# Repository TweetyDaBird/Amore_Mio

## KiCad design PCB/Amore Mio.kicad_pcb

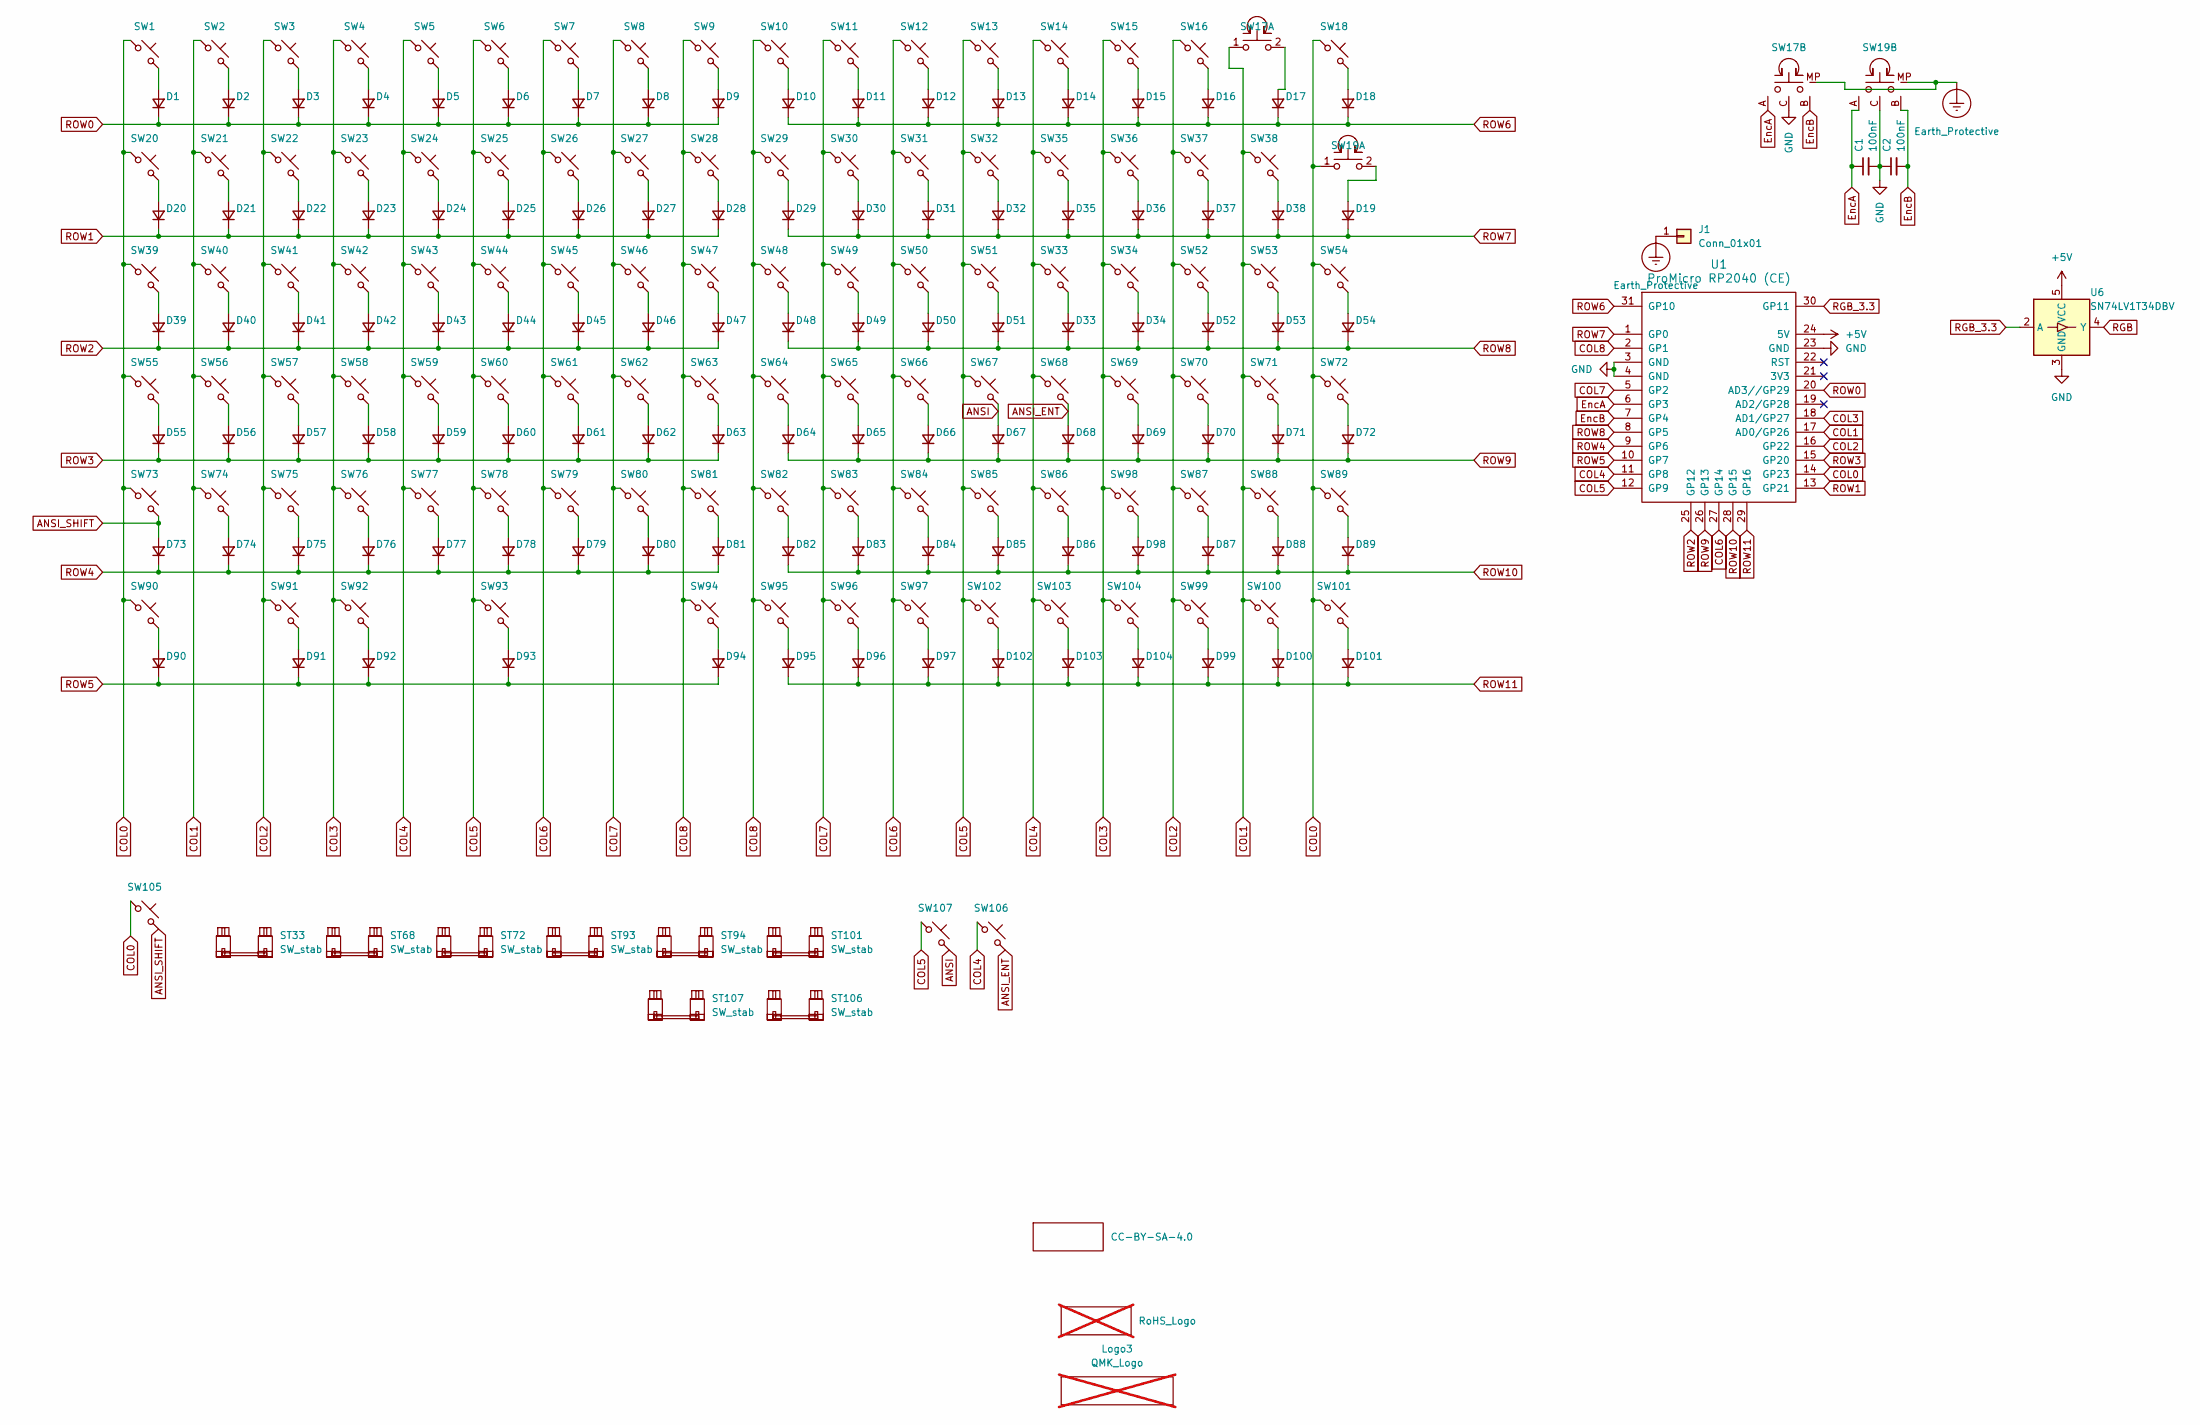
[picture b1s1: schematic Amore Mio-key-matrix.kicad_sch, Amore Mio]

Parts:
C1, C2: 100nF; C_Axial_L5.1mm_D3.1mm_P7.50mm_Horizontal; LCSC C513772
D1, D2, D3, D4, D5, D6, D7, D8, D9, D10, D11, D12, D13, D14, D15, D16, D17, D18, D19, D20, D21, D22, D23, D24, D25, D26, D27, D28, D29, D30, D31, D32, D33, D34, D35, D36, D37, D38, D39, D40, D41, D42, D43, D44, D45, D46, D47, D48, D49, D50, D51, D52, D53, D54, D55, D56, D57, D58, D59, D60, D61, D62, D63, D64, D65, D66, D67, D68, D69, D70, D71, D72, D73, D74, D75, D76, D77, D78, D79, D80, D81, D82, D83, D84, D85, D86, D87, D88, D89, D90, D91, D92, D93, D94, D95, D96, D97, D98, D99, D100, D101, D102, D103, D104: D; D_SOD-123
J1: Conn_01x01; PinHeader_1x01_P2.54mm_Vertical
Logo1: CC-BY-SA-4.0; CC_BY_SA_40_line
Logo2: RoHS_Logo; RoHs; not fitted
Logo3: QMK_Logo; Powered_by_QMK; not fitted
ST33, ST68, ST72, ST93, ST94, ST101, ST106, ST107: SW_stab; Stabilizer_Cherry_MX_2.00u
SW1, SW2, SW3, SW4, SW5, SW6, SW7, SW8, SW9, SW10, SW11, SW12, SW13, SW14, SW15, SW16, SW18, SW20, SW21, SW22, SW23, SW24, SW25, SW26, SW27, SW28, SW29, SW30, SW31, SW32, SW34, SW35, SW36, SW37, SW38, SW40, SW41, SW42, SW43, SW44, SW45, SW46, SW47, SW48, SW49, SW50, SW51, SW52, SW53, SW54, SW56, SW57, SW58, SW59, SW60, SW61, SW62, SW63, SW64, SW65, SW66, SW67, SW69, SW70, SW71, SW74, SW75, SW76, SW77, SW78, SW79, SW80, SW81, SW82, SW83, SW84, SW85, SW87, SW88, SW89, SW96, SW98, SW99, SW100, SW102, SW103, SW104: SW_Push; SW_MX_HotSwap
SW17, SW19: SW_Push; SW_MX_HotSwap_Encoder
SW33: SW_Push; SW_MX_HotSwap_2.00u
SW39, SW90, SW107: SW_Push; SW_MX_HotSwap_1.50u
SW55, SW86: SW_Push; SW_MX_HotSwap_1.75u
SW68: SW_Push; SW_MX_HotSwap_ISO_Enter_flipped
SW72, SW101: SW_Push; SW_MX_HotSwap_Vertical_2.00u
SW73, SW91, SW92, SW95, SW97: SW_Push; SW_MX_HotSwap_1.25u
SW93, SW105, SW106: SW_Push; SW_MX_HotSwap_2.25u
SW94: SW_Push; SW_MX_HotSwap_2.75u
U1: ProMicro RP2040 (CE); ProMicro RP2040CE
U6: SN74LV1T34DBV; SOT-23-5; LCSC C100024

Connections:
+5V: U1.24 (5V), U6.5 (VCC); also elsewhere on the board
ANSI: D67.2 (A), SW67.2, SW107.2
ANSI_ENT: D68.2 (A), SW68.2, SW106.2
ANSI_SHIFT: D73.2 (A), SW73.2, SW105.2
COL0: SW1.1, SW18.1, SW19.1, SW19.S1, SW20.1, SW39.1, SW54.1, SW55.1, SW72.1, SW73.1, SW89.1, SW90.1, SW101.1, SW105.1, U1.14 (GP23)
COL1: SW2.1, SW17.1, SW17.S1, SW21.1, SW38.1, SW40.1, SW53.1, SW56.1, SW71.1, SW74.1, SW88.1, SW100.1, U1.17 (AD0/GP26)
COL2: SW3.1, SW16.1, SW22.1, SW37.1, SW41.1, SW52.1, SW57.1, SW70.1, SW75.1, SW87.1, SW91.1, SW99.1, U1.16 (GP22)
COL3: SW4.1, SW15.1, SW23.1, SW34.1, SW36.1, SW42.1, SW58.1, SW69.1, SW76.1, SW92.1, SW98.1, SW104.1, U1.18 (AD1/GP27)
COL4: SW5.1, SW14.1, SW24.1, SW33.1, SW35.1, SW43.1, SW59.1, SW68.1, SW77.1, SW86.1, SW103.1, SW106.1, U1.11 (GP8)
COL5: SW6.1, SW13.1, SW25.1, SW32.1, SW44.1, SW51.1, SW60.1, SW67.1, SW78.1, SW85.1, SW93.1, SW102.1, SW107.1, U1.12 (GP9)
COL6: SW7.1, SW12.1, SW26.1, SW31.1, SW45.1, SW50.1, SW61.1, SW66.1, SW79.1, SW84.1, SW97.1, U1.27 (GP14)
COL7: SW8.1, SW11.1, SW27.1, SW30.1, SW46.1, SW49.1, SW62.1, SW65.1, SW80.1, SW83.1, SW96.1, U1.5 (GP2)
COL8: SW9.1, SW10.1, SW28.1, SW29.1, SW47.1, SW48.1, SW63.1, SW64.1, SW81.1, SW82.1, SW94.1, SW95.1, U1.2 (GP1)
EncA: C1.1, SW17.A, SW19.A, U1.6 (GP3)
EncB: C2.2, SW17.B, SW19.B, U1.7 (GP4)
unnamed: D1.2 (A), SW1.2
unnamed: D2.2 (A), SW2.2
unnamed: D3.2 (A), SW3.2
unnamed: D4.2 (A), SW4.2
unnamed: D5.2 (A), SW5.2
unnamed: D6.2 (A), SW6.2
unnamed: D7.2 (A), SW7.2
unnamed: D8.2 (A), SW8.2
unnamed: D9.2 (A), SW9.2
unnamed: D10.2 (A), SW10.2
unnamed: D11.2 (A), SW11.2
unnamed: D12.2 (A), SW12.2
unnamed: D13.2 (A), SW13.2
unnamed: D14.2 (A), SW14.2
unnamed: D15.2 (A), SW15.2
unnamed: D16.2 (A), SW16.2
unnamed: D17.2 (A), SW17.2, SW17.S2
unnamed: D18.2 (A), SW18.2
unnamed: D19.2 (A), SW19.2, SW19.S2
unnamed: D20.2 (A), SW20.2
unnamed: D21.2 (A), SW21.2
unnamed: D22.2 (A), SW22.2
unnamed: D23.2 (A), SW23.2
unnamed: D24.2 (A), SW24.2
unnamed: D25.2 (A), SW25.2
unnamed: D26.2 (A), SW26.2
unnamed: D27.2 (A), SW27.2
unnamed: D28.2 (A), SW28.2
unnamed: D29.2 (A), SW29.2
unnamed: D30.2 (A), SW30.2
unnamed: D31.2 (A), SW31.2
unnamed: D32.2 (A), SW32.2
unnamed: D33.2 (A), SW33.2
unnamed: D34.2 (A), SW34.2
unnamed: D35.2 (A), SW35.2
unnamed: D36.2 (A), SW36.2
unnamed: D37.2 (A), SW37.2
unnamed: D38.2 (A), SW38.2
unnamed: D39.2 (A), SW39.2
unnamed: D40.2 (A), SW40.2
unnamed: D41.2 (A), SW41.2
unnamed: D42.2 (A), SW42.2
unnamed: D43.2 (A), SW43.2
unnamed: D44.2 (A), SW44.2
unnamed: D45.2 (A), SW45.2
unnamed: D46.2 (A), SW46.2
unnamed: D47.2 (A), SW47.2
unnamed: D48.2 (A), SW48.2
unnamed: D49.2 (A), SW49.2
unnamed: D50.2 (A), SW50.2
unnamed: D51.2 (A), SW51.2
unnamed: D52.2 (A), SW52.2
unnamed: D53.2 (A), SW53.2
unnamed: D54.2 (A), SW54.2
unnamed: D55.2 (A), SW55.2
unnamed: D56.2 (A), SW56.2
unnamed: D57.2 (A), SW57.2
unnamed: D58.2 (A), SW58.2
unnamed: D59.2 (A), SW59.2
unnamed: D60.2 (A), SW60.2
unnamed: D61.2 (A), SW61.2
unnamed: D62.2 (A), SW62.2
unnamed: D63.2 (A), SW63.2
unnamed: D64.2 (A), SW64.2
unnamed: D65.2 (A), SW65.2
unnamed: D66.2 (A), SW66.2
unnamed: D69.2 (A), SW69.2
unnamed: D70.2 (A), SW70.2
unnamed: D71.2 (A), SW71.2
unnamed: D72.2 (A), SW72.2
unnamed: D74.2 (A), SW74.2
unnamed: D75.2 (A), SW75.2
unnamed: D76.2 (A), SW76.2
unnamed: D77.2 (A), SW77.2
unnamed: D78.2 (A), SW78.2
unnamed: D79.2 (A), SW79.2
unnamed: D80.2 (A), SW80.2
unnamed: D81.2 (A), SW81.2
unnamed: D82.2 (A), SW82.2
unnamed: D83.2 (A), SW83.2
unnamed: D84.2 (A), SW84.2
unnamed: D85.2 (A), SW85.2
unnamed: D86.2 (A), SW86.2
unnamed: D87.2 (A), SW87.2
unnamed: D88.2 (A), SW88.2
unnamed: D89.2 (A), SW89.2
unnamed: D90.2 (A), SW90.2
unnamed: D91.2 (A), SW91.2
unnamed: D92.2 (A), SW92.2
unnamed: D93.2 (A), SW93.2
unnamed: D94.2 (A), SW94.2
unnamed: D95.2 (A), SW95.2
unnamed: D96.2 (A), SW96.2
unnamed: D97.2 (A), SW97.2
unnamed: D98.2 (A), SW98.2
unnamed: D99.2 (A), SW99.2
unnamed: D100.2 (A), SW100.2
unnamed: D101.2 (A), SW101.2
unnamed: D102.2 (A), SW102.2
unnamed: D103.2 (A), SW103.2
unnamed: D104.2 (A), SW104.2
RGB: U6.4 (Y); also elsewhere on the board
RGB_3.3: U1.30 (GP11), U6.2 (A)
ROW0: D1.1 (K), D2.1 (K), D3.1 (K), D4.1 (K), D5.1 (K), D6.1 (K), D7.1 (K), D8.1 (K), D9.1 (K), U1.20 (AD3//GP29)
ROW1: D20.1 (K), D21.1 (K), D22.1 (K), D23.1 (K), D24.1 (K), D25.1 (K), D26.1 (K), D27.1 (K), D28.1 (K), U1.13 (GP21)
ROW2: D39.1 (K), D40.1 (K), D41.1 (K), D42.1 (K), D43.1 (K), D44.1 (K), D45.1 (K), D46.1 (K), D47.1 (K), U1.25 (GP12)
ROW3: D55.1 (K), D56.1 (K), D57.1 (K), D58.1 (K), D59.1 (K), D60.1 (K), D61.1 (K), D62.1 (K), D63.1 (K), U1.15 (GP20)
ROW4: D73.1 (K), D74.1 (K), D75.1 (K), D76.1 (K), D77.1 (K), D78.1 (K), D79.1 (K), D80.1 (K), D81.1 (K), U1.9 (GP6)
ROW5: D90.1 (K), D91.1 (K), D92.1 (K), D93.1 (K), D94.1 (K), U1.10 (GP7)
ROW6: D10.1 (K), D11.1 (K), D12.1 (K), D13.1 (K), D14.1 (K), D15.1 (K), D16.1 (K), D17.1 (K), D18.1 (K), U1.31 (GP10)
ROW7: D19.1 (K), D29.1 (K), D30.1 (K), D31.1 (K), D32.1 (K), D35.1 (K), D36.1 (K), D37.1 (K), D38.1 (K), U1.1 (GP0)
ROW8: D33.1 (K), D34.1 (K), D48.1 (K), D49.1 (K), D50.1 (K), D51.1 (K), D52.1 (K), D53.1 (K), D54.1 (K), U1.8 (GP5)
ROW9: D64.1 (K), D65.1 (K), D66.1 (K), D67.1 (K), D68.1 (K), D69.1 (K), D70.1 (K), D71.1 (K), D72.1 (K), U1.26 (GP13)
ROW10: D82.1 (K), D83.1 (K), D84.1 (K), D85.1 (K), D86.1 (K), D87.1 (K), D88.1 (K), D89.1 (K), D98.1 (K), U1.28 (GP15)
ROW11: D95.1 (K), D96.1 (K), D97.1 (K), D99.1 (K), D100.1 (K), D101.1 (K), D102.1 (K), D103.1 (K), D104.1 (K), U1.29 (GP16)

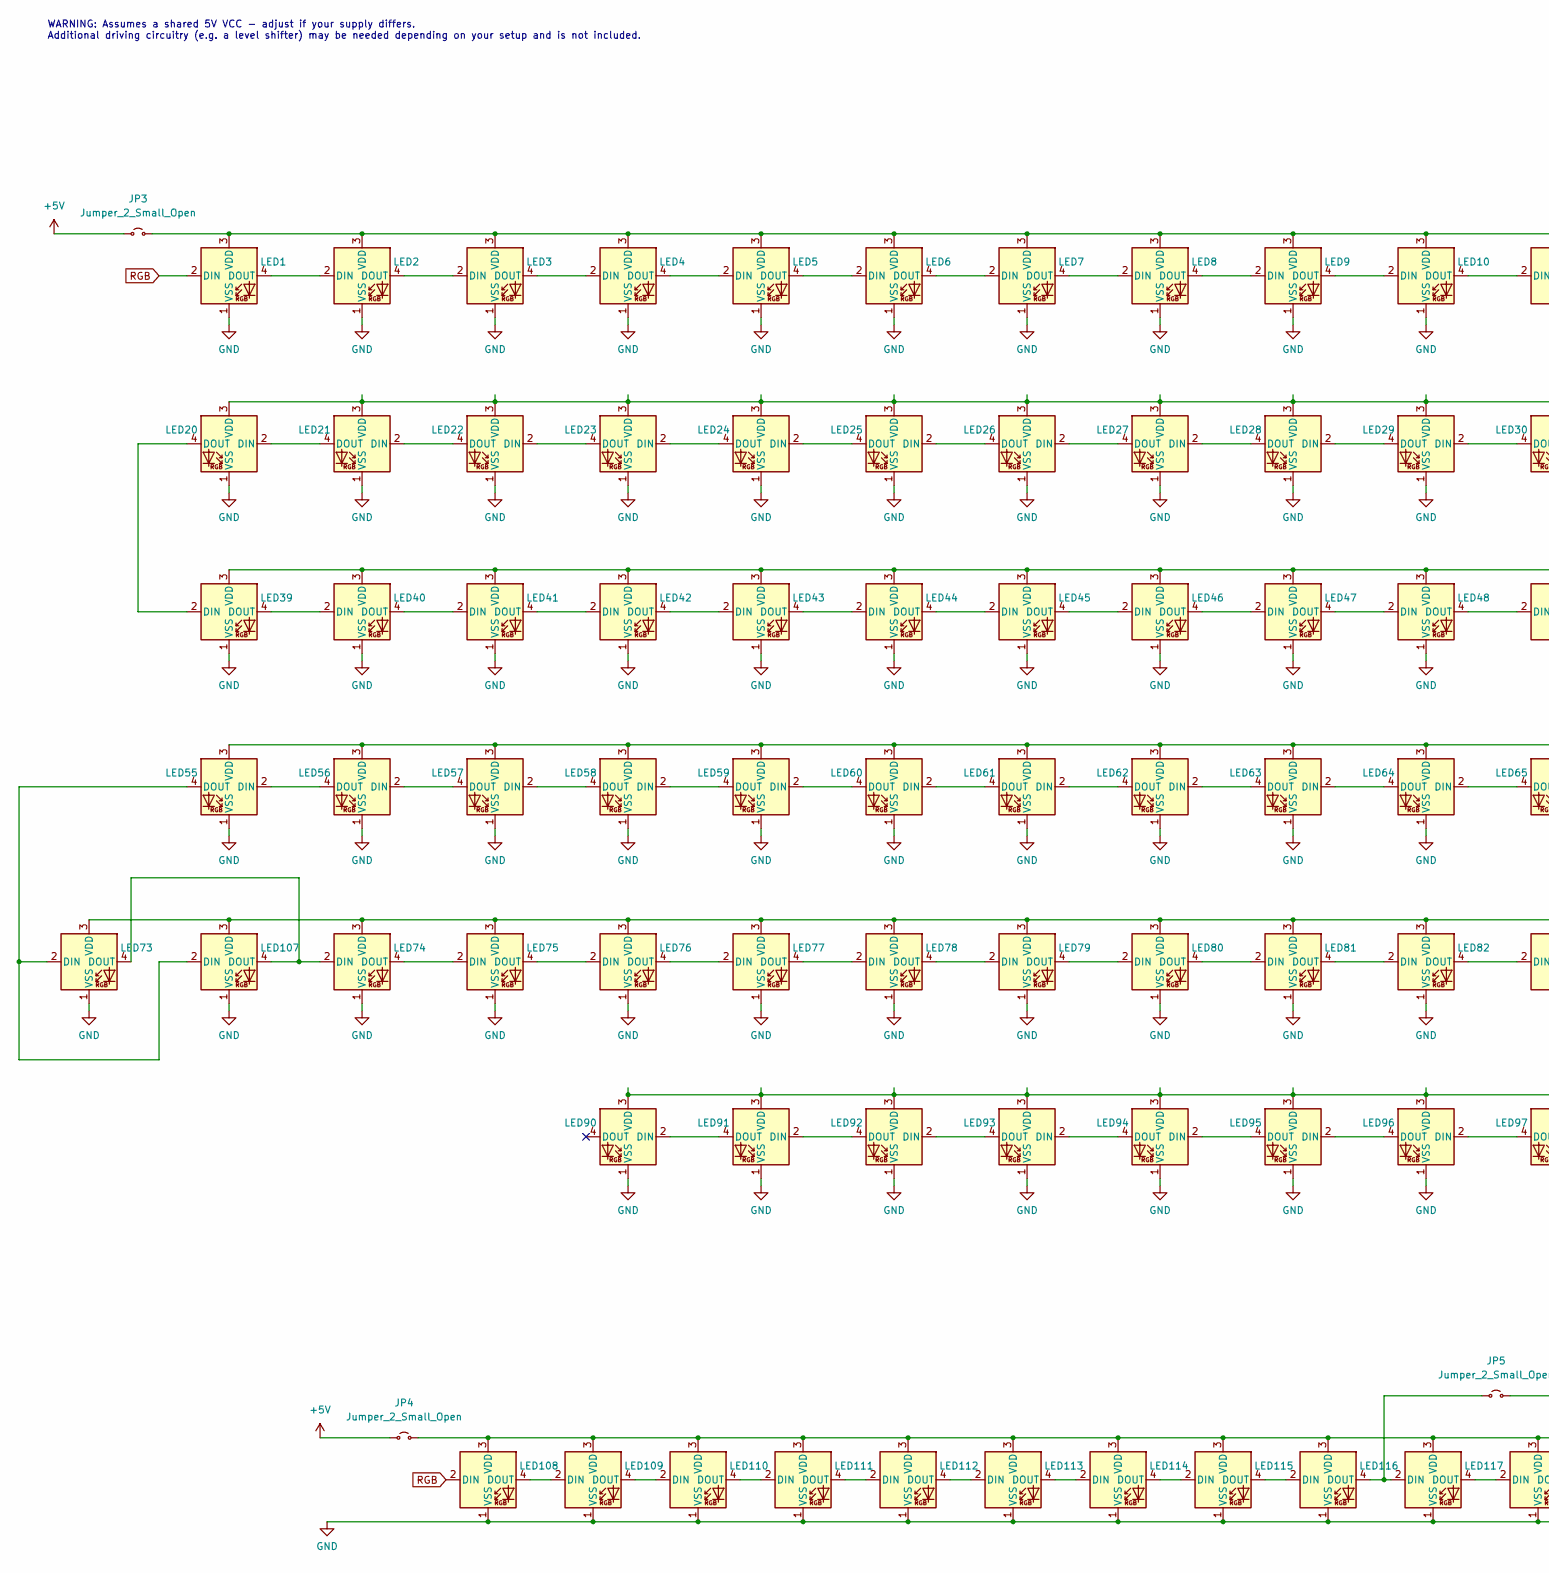
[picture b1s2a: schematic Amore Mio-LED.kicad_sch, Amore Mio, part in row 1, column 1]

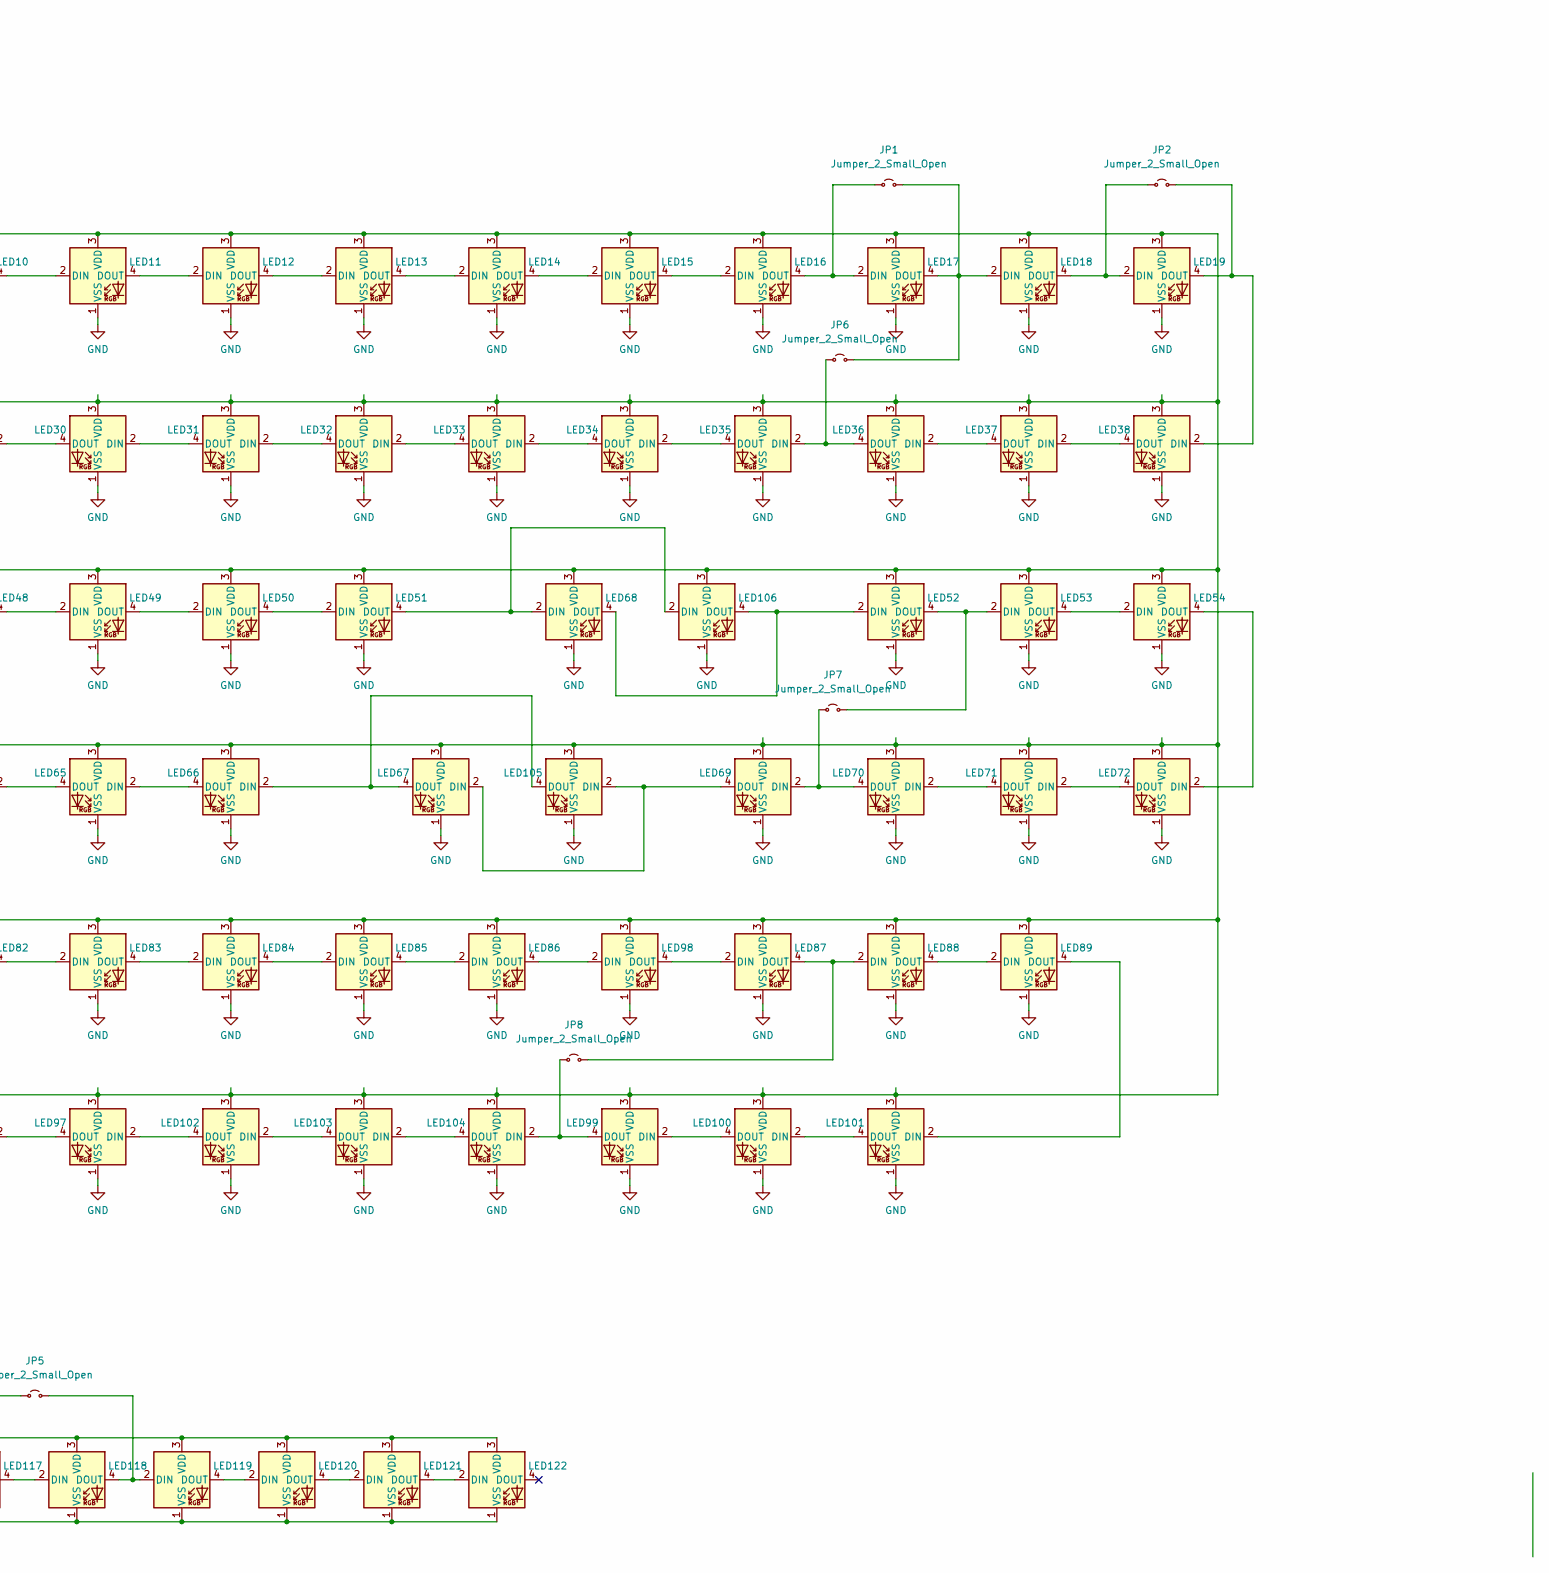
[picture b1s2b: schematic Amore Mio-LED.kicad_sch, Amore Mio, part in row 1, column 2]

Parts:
JP1, JP2, JP3, JP4, JP5, JP6, JP7, JP8: Jumper_2_Small_Open; Jumper_min_v2
LED1, LED2, LED3, LED4, LED5, LED6, LED7, LED8, LED9, LED10, LED11, LED12, LED13, LED14, LED15, LED16, LED17, LED18, LED19, LED20, LED21, LED22, LED23, LED24, LED25, LED26, LED27, LED28, LED29, LED30, LED31, LED32, LED33, LED34, LED35, LED36, LED37, LED38, LED39, LED40, LED41, LED42, LED43, LED44, LED45, LED46, LED47, LED48, LED49, LED50, LED51, LED52, LED53, LED54, LED55, LED56, LED57, LED58, LED59, LED60, LED61, LED62, LED63, LED64, LED65, LED66, LED67, LED68, LED69, LED70, LED71, LED72, LED73, LED74, LED75, LED76, LED77, LED78, LED79, LED80, LED81, LED82, LED83, LED84, LED85, LED86, LED87, LED88, LED89, LED90, LED91, LED92, LED93, LED94, LED95, LED96, LED97, LED98, LED99, LED100, LED101, LED102, LED103, LED104, LED105, LED106, LED107, LED108, LED109, LED110, LED111, LED112, LED113, LED114, LED115, LED116, LED117, LED118, LED119, LED120, LED121, LED122: SK6812MINI-E; MX_SK6812MINI-E_SMALL_PAD

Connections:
+5V: JP3.1 (A), JP4.1 (A); also elsewhere on the board
unnamed: JP1.1 (A), LED16.4 (DOUT), LED17.2 (DIN)
unnamed: JP1.2 (B), JP6.2 (B), LED17.4 (DOUT), LED18.2 (DIN)
unnamed: JP2.1 (A), LED18.4 (DOUT), LED19.2 (DIN)
unnamed: JP2.2 (B), LED19.4 (DOUT), LED38.2 (DIN)
unnamed: JP3.2 (B), LED1.3 (VDD), LED2.3 (VDD), LED3.3 (VDD), LED4.3 (VDD), LED5.3 (VDD), LED6.3 (VDD), LED7.3 (VDD), LED8.3 (VDD), LED9.3 (VDD), LED10.3 (VDD), LED11.3 (VDD), LED12.3 (VDD), LED13.3 (VDD), LED14.3 (VDD), LED15.3 (VDD), LED16.3 (VDD), LED17.3 (VDD), LED18.3 (VDD), LED19.3 (VDD), LED20.3 (VDD), LED21.3 (VDD), LED22.3 (VDD), LED23.3 (VDD), LED24.3 (VDD), LED25.3 (VDD), LED26.3 (VDD), LED27.3 (VDD), LED28.3 (VDD), LED29.3 (VDD), LED30.3 (VDD), LED31.3 (VDD), LED32.3 (VDD), LED33.3 (VDD), LED34.3 (VDD), LED35.3 (VDD), LED36.3 (VDD), LED37.3 (VDD), LED38.3 (VDD), LED39.3 (VDD), LED40.3 (VDD), LED41.3 (VDD), LED42.3 (VDD), LED43.3 (VDD), LED44.3 (VDD), LED45.3 (VDD), LED46.3 (VDD), LED47.3 (VDD), LED48.3 (VDD), LED49.3 (VDD), LED50.3 (VDD), LED51.3 (VDD), LED52.3 (VDD), LED53.3 (VDD), LED54.3 (VDD), LED55.3 (VDD), LED56.3 (VDD), LED57.3 (VDD), LED58.3 (VDD), LED59.3 (VDD), LED60.3 (VDD), LED61.3 (VDD), LED62.3 (VDD), LED63.3 (VDD), LED64.3 (VDD), LED65.3 (VDD), LED66.3 (VDD), LED67.3 (VDD), LED68.3 (VDD), LED69.3 (VDD), LED70.3 (VDD), LED71.3 (VDD), LED72.3 (VDD), LED73.3 (VDD), LED74.3 (VDD), LED75.3 (VDD), LED76.3 (VDD), LED77.3 (VDD), LED78.3 (VDD), LED79.3 (VDD), LED80.3 (VDD), LED81.3 (VDD), LED82.3 (VDD), LED83.3 (VDD), LED84.3 (VDD), LED85.3 (VDD), LED86.3 (VDD), LED87.3 (VDD), LED88.3 (VDD), LED89.3 (VDD), LED90.3 (VDD), LED91.3 (VDD), LED92.3 (VDD), LED93.3 (VDD), LED94.3 (VDD), LED95.3 (VDD), LED96.3 (VDD), LED97.3 (VDD), LED98.3 (VDD), LED99.3 (VDD), LED100.3 (VDD), LED101.3 (VDD), LED102.3 (VDD), LED103.3 (VDD), LED104.3 (VDD), LED105.3 (VDD), LED106.3 (VDD), LED107.3 (VDD)
unnamed: JP4.2 (B), LED108.3 (VDD), LED109.3 (VDD), LED110.3 (VDD), LED111.3 (VDD), LED112.3 (VDD), LED113.3 (VDD), LED114.3 (VDD), LED115.3 (VDD), LED116.3 (VDD), LED117.3 (VDD), LED118.3 (VDD), LED119.3 (VDD), LED120.3 (VDD), LED121.3 (VDD), LED122.3 (VDD)
unnamed: JP5.1 (A), LED116.4 (DOUT), LED117.2 (DIN)
unnamed: JP5.2 (B), LED118.4 (DOUT), LED119.2 (DIN)
unnamed: JP6.1 (A), LED35.2 (DIN), LED36.4 (DOUT)
unnamed: JP7.1 (A), LED69.2 (DIN), LED70.4 (DOUT)
unnamed: JP7.2 (B), LED52.4 (DOUT), LED53.2 (DIN)
unnamed: JP8.1 (A), LED99.4 (DOUT), LED104.2 (DIN)
unnamed: JP8.2 (B), LED87.4 (DOUT), LED88.2 (DIN)
unnamed: LED1.4 (DOUT), LED2.2 (DIN)
unnamed: LED2.4 (DOUT), LED3.2 (DIN)
unnamed: LED3.4 (DOUT), LED4.2 (DIN)
unnamed: LED4.4 (DOUT), LED5.2 (DIN)
unnamed: LED5.4 (DOUT), LED6.2 (DIN)
unnamed: LED6.4 (DOUT), LED7.2 (DIN)
unnamed: LED7.4 (DOUT), LED8.2 (DIN)
unnamed: LED8.4 (DOUT), LED9.2 (DIN)
unnamed: LED9.4 (DOUT), LED10.2 (DIN)
unnamed: LED10.4 (DOUT), LED11.2 (DIN)
unnamed: LED11.4 (DOUT), LED12.2 (DIN)
unnamed: LED12.4 (DOUT), LED13.2 (DIN)
unnamed: LED13.4 (DOUT), LED14.2 (DIN)
unnamed: LED14.4 (DOUT), LED15.2 (DIN)
unnamed: LED15.4 (DOUT), LED16.2 (DIN)
unnamed: LED20.2 (DIN), LED21.4 (DOUT)
unnamed: LED20.4 (DOUT), LED39.2 (DIN)
unnamed: LED21.2 (DIN), LED22.4 (DOUT)
unnamed: LED22.2 (DIN), LED23.4 (DOUT)
unnamed: LED23.2 (DIN), LED24.4 (DOUT)
unnamed: LED24.2 (DIN), LED25.4 (DOUT)
unnamed: LED25.2 (DIN), LED26.4 (DOUT)
unnamed: LED26.2 (DIN), LED27.4 (DOUT)
unnamed: LED27.2 (DIN), LED28.4 (DOUT)
unnamed: LED28.2 (DIN), LED29.4 (DOUT)
unnamed: LED29.2 (DIN), LED30.4 (DOUT)
unnamed: LED30.2 (DIN), LED31.4 (DOUT)
unnamed: LED31.2 (DIN), LED32.4 (DOUT)
unnamed: LED32.2 (DIN), LED33.4 (DOUT)
unnamed: LED33.2 (DIN), LED34.4 (DOUT)
unnamed: LED34.2 (DIN), LED35.4 (DOUT)
unnamed: LED36.2 (DIN), LED37.4 (DOUT)
unnamed: LED37.2 (DIN), LED38.4 (DOUT)
unnamed: LED39.4 (DOUT), LED40.2 (DIN)
unnamed: LED40.4 (DOUT), LED41.2 (DIN)
unnamed: LED41.4 (DOUT), LED42.2 (DIN)
unnamed: LED42.4 (DOUT), LED43.2 (DIN)
unnamed: LED43.4 (DOUT), LED44.2 (DIN)
unnamed: LED44.4 (DOUT), LED45.2 (DIN)
unnamed: LED45.4 (DOUT), LED46.2 (DIN)
unnamed: LED46.4 (DOUT), LED47.2 (DIN)
unnamed: LED47.4 (DOUT), LED48.2 (DIN)
unnamed: LED48.4 (DOUT), LED49.2 (DIN)
unnamed: LED49.4 (DOUT), LED50.2 (DIN)
unnamed: LED50.4 (DOUT), LED51.2 (DIN)
unnamed: LED53.4 (DOUT), LED54.2 (DIN)
unnamed: LED54.4 (DOUT), LED72.2 (DIN)
unnamed: LED55.2 (DIN), LED56.4 (DOUT)
unnamed: LED56.2 (DIN), LED57.4 (DOUT)
unnamed: LED57.2 (DIN), LED58.4 (DOUT)
unnamed: LED58.2 (DIN), LED59.4 (DOUT)
unnamed: LED59.2 (DIN), LED60.4 (DOUT)
unnamed: LED60.2 (DIN), LED61.4 (DOUT)
unnamed: LED61.2 (DIN), LED62.4 (DOUT)
unnamed: LED62.2 (DIN), LED63.4 (DOUT)
unnamed: LED63.2 (DIN), LED64.4 (DOUT)
unnamed: LED64.2 (DIN), LED65.4 (DOUT)
unnamed: LED65.2 (DIN), LED66.4 (DOUT)
unnamed: LED70.2 (DIN), LED71.4 (DOUT)
unnamed: LED71.2 (DIN), LED72.4 (DOUT)
unnamed: LED74.4 (DOUT), LED75.2 (DIN)
unnamed: LED75.4 (DOUT), LED76.2 (DIN)
unnamed: LED76.4 (DOUT), LED77.2 (DIN)
unnamed: LED77.4 (DOUT), LED78.2 (DIN)
unnamed: LED78.4 (DOUT), LED79.2 (DIN)
unnamed: LED79.4 (DOUT), LED80.2 (DIN)
unnamed: LED80.4 (DOUT), LED81.2 (DIN)
unnamed: LED81.4 (DOUT), LED82.2 (DIN)
unnamed: LED82.4 (DOUT), LED83.2 (DIN)
unnamed: LED83.4 (DOUT), LED84.2 (DIN)
unnamed: LED84.4 (DOUT), LED85.2 (DIN)
unnamed: LED85.4 (DOUT), LED86.2 (DIN)
unnamed: LED86.4 (DOUT), LED98.2 (DIN)
unnamed: LED87.2 (DIN), LED98.4 (DOUT)
unnamed: LED88.4 (DOUT), LED89.2 (DIN)
unnamed: LED90.2 (DIN), LED91.4 (DOUT)
unnamed: LED91.2 (DIN), LED92.4 (DOUT)
unnamed: LED92.2 (DIN), LED93.4 (DOUT)
unnamed: LED93.2 (DIN), LED94.4 (DOUT)
unnamed: LED94.2 (DIN), LED95.4 (DOUT)
unnamed: LED95.2 (DIN), LED96.4 (DOUT)
unnamed: LED96.2 (DIN), LED97.4 (DOUT)
unnamed: LED100.2 (DIN), LED101.4 (DOUT)
unnamed: LED99.2 (DIN), LED100.4 (DOUT)
unnamed: LED89.4 (DOUT), LED101.2 (DIN)
unnamed: LED102.2 (DIN), LED103.4 (DOUT)
unnamed: LED97.2 (DIN), LED102.4 (DOUT)
unnamed: LED103.2 (DIN), LED104.4 (DOUT)
unnamed: LED67.2 (DIN), LED69.4 (DOUT), LED105.2 (DIN)
unnamed: LED66.2 (DIN), LED67.4 (DOUT), LED105.4 (DOUT)
unnamed: LED51.4 (DOUT), LED68.2 (DIN), LED106.2 (DIN)
unnamed: LED52.2 (DIN), LED68.4 (DOUT), LED106.4 (DOUT)
unnamed: LED55.4 (DOUT), LED73.2 (DIN), LED107.2 (DIN)
unnamed: LED73.4 (DOUT), LED74.2 (DIN), LED107.4 (DOUT)
unnamed: LED108.4 (DOUT), LED109.2 (DIN)
unnamed: LED109.4 (DOUT), LED110.2 (DIN)
unnamed: LED110.4 (DOUT), LED111.2 (DIN)
unnamed: LED111.4 (DOUT), LED112.2 (DIN)
unnamed: LED112.4 (DOUT), LED113.2 (DIN)
unnamed: LED113.4 (DOUT), LED114.2 (DIN)
unnamed: LED114.4 (DOUT), LED115.2 (DIN)
unnamed: LED115.4 (DOUT), LED116.2 (DIN)
unnamed: LED117.4 (DOUT), LED118.2 (DIN)
unnamed: LED119.4 (DOUT), LED120.2 (DIN)
unnamed: LED120.4 (DOUT), LED121.2 (DIN)
unnamed: LED121.4 (DOUT), LED122.2 (DIN)
RGB: LED1.2 (DIN), LED108.2 (DIN); also elsewhere on the board

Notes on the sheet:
WARNING: Assumes a shared 5V VCC - adjust if your supply differs. Additional driving circuitry (e.g. a level shifter) may be needed depending on your setup and is not included.

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
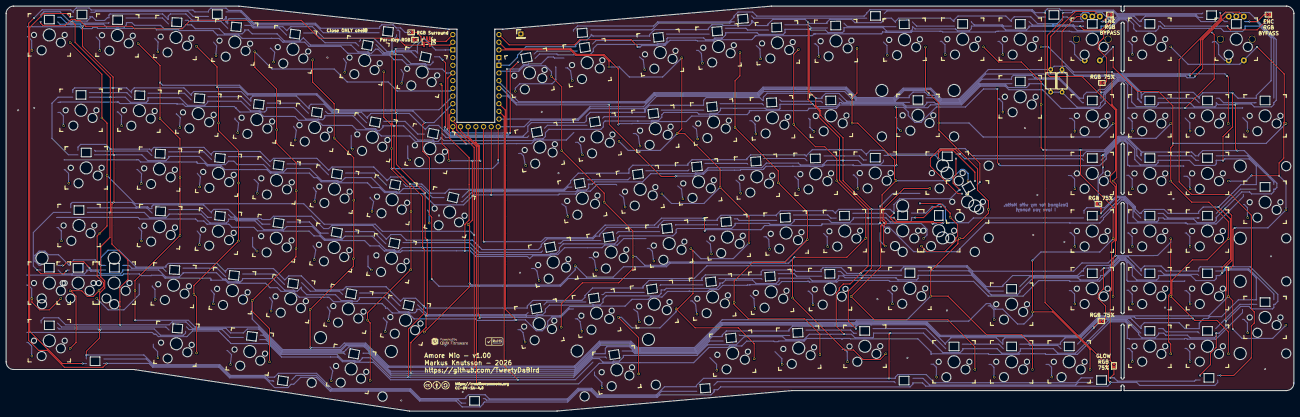
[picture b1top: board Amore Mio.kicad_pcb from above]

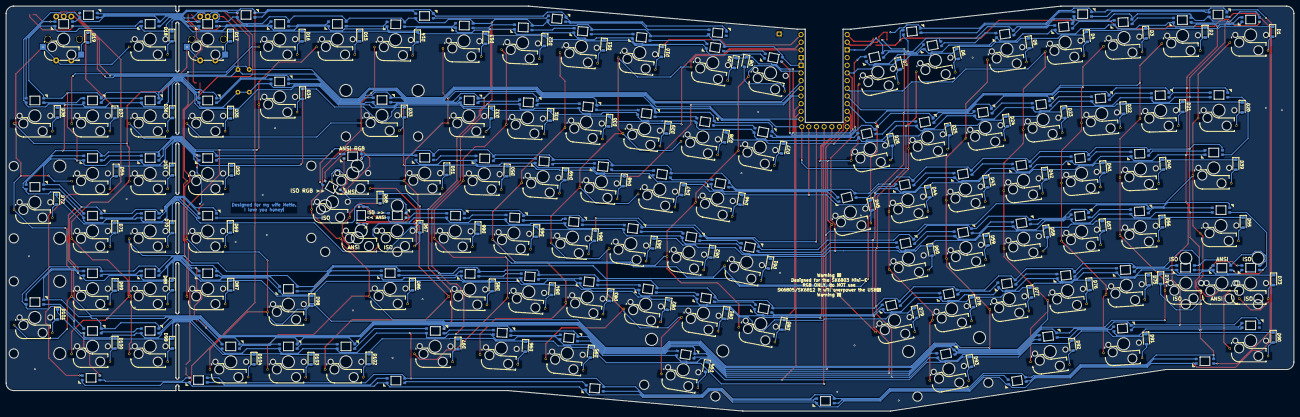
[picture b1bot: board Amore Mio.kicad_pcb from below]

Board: 2 copper layers, 425.9 x 133.9 mm, 357 parts (105 on the bottom side), 251 nets.

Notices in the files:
PCB/Amore Mio-LED.kicad_sch:
Licensed under Creative Commons BY-SA 4.0 International
